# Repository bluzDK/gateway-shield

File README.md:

Bluz Gateway Shield Hardware Files
==========
Bluz is a Development Kit (DK) that implements the Wiring language and talks to the [Particle](https://www.particle.io/) cloud through Bluetooth Low Energy. It can be accessed through a REST API and programmed from a Web IDE.

These files have been made available online through a [Creative Commons Attribution-ShareAlike 3.0](http://creativecommons.org/licenses/by-sa/3.0/) license.

You are welcome to distribute, remix, and use these files for commercial purposes. If you do so, please attribute the original design to Bluz both on the website and on the physical packaging of the product or in the instruction manual. All derivative works must be published under the same or a similar license.

All items are subject to change over time as the product is designed, so make sure you are always looking at the latest information by pulling often.

##Sections
<b>BOM</b>: Current Bill of Materials for the gateway shield.

<b>Datasheets</b>: Datasheets for all major parts on the board.

<b>HW Design</b>: Schematics, board layouts, and other design files.

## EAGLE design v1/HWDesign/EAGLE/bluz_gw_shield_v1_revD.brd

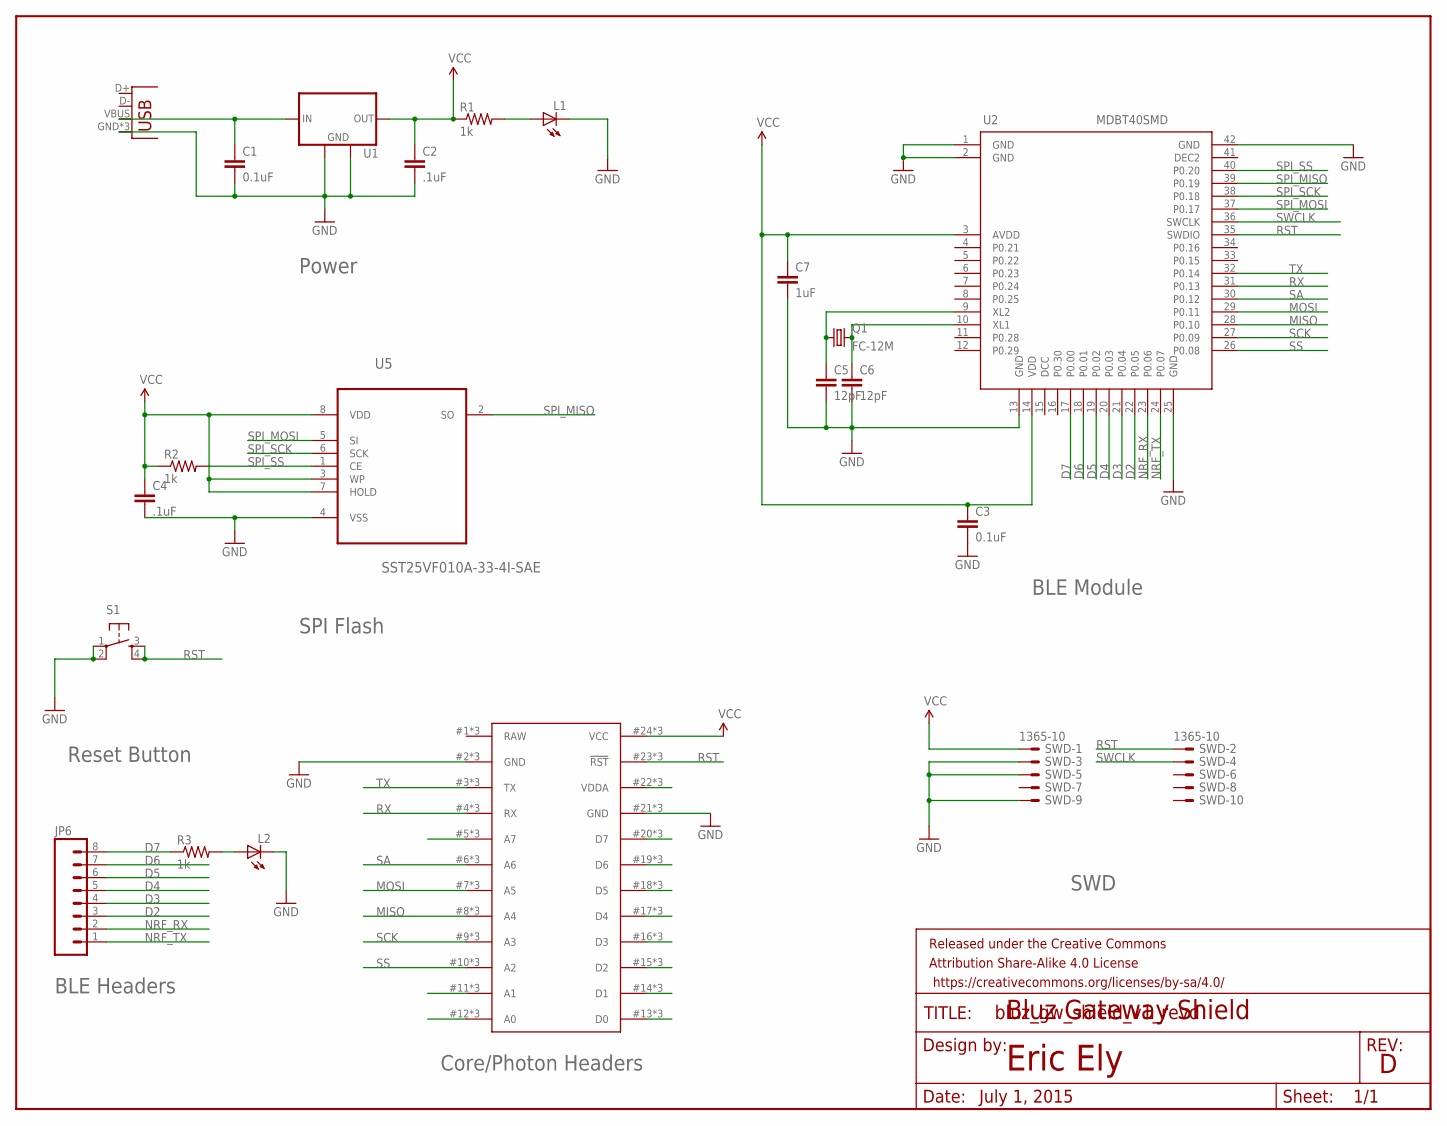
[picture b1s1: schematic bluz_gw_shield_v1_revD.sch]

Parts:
C1, C3: 0.1uF; 0603-CAP
C2, C4: .1uF; 0603-CAP
C5, C6: 12pF; 0603-CAP
C7: 1uF; 0603-CAP
FRAME1: FRAME-LETTER; CREATIVE_COMMONS
J2: USB-MICROB
JP6: M081X08; 1X08
L1, L2: LEDCHIP-LED0603; CHIP-LED0603
Q1: FC-12M
R1, R2, R3: 1k; 0603-RES
S1: TAC_SWITCHSMD; TACTILE_SWITCH_SMD
SWD: 1365-10
U1: MCP1825S-SOT223; SOT223
U2: MDBT40SMD; MDBT40
U4: SPARK_CORE; SPARK_CORE_STACKABLE
U5: SST25VF010A-33-4I-SAE; SOIC127P600X175-8N

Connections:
D2: JP6.3, U2.22 (P0.05)
D3: JP6.4, U2.21 (P0.04)
D4: JP6.5, U2.20 (P0.03)
D5: JP6.6, U2.19 (P0.02)
D6: JP6.7, U2.18 (P0.01)
D7: JP6.8, R3.1, U2.17 (P0.00)
GND: C1.2, C2.2, C3.2, C4.2, C5.2, C6.2, C7.2, J2.GND, J2.MT1 (GND), J2.MT2 (GND), L1.C, L2.C, S1.1, S1.2, SWD.3, SWD.5, SWD.9, U1.2 (GND), U1.4 (GND), U2.1 (GND), U2.2 (GND), U2.13 (GND), U2.25 (GND), U2.42 (GND), U4.2 (GND), U4.21 (GND), U4.#2 (GND), U4.#21 (GND), U4.@2 (GND), U4.@21 (GND), U5.4 (VSS)
MISO: U2.28 (P0.10), U4.8 (A4), U4.#8 (A4), U4.@8 (A4)
MOSI: U2.29 (P0.11), U4.7 (A5), U4.#7 (A5), U4.@7 (A5)
unnamed: C1.1, J2.VBUS, U1.1 (IN)
unnamed: L2.A, R3.2
unnamed: U4.5 (A7), U4.#5 (A7), U4.@5 (A7)
unnamed: U4.11 (A1), U4.#11 (A1), U4.@11 (A1)
unnamed: L1.A, R1.2
unnamed: U4.12 (A0), U4.#12 (A0), U4.@12 (A0)
unnamed: C5.1, Q1.1, U2.9 (XL2)
unnamed: C6.1, Q1.2, U2.10 (XL1)
unnamed: U4.13 (D0), U4.#13 (D0), U4.@13 (D0)
unnamed: U4.14 (D1), U4.#14 (D1), U4.@14 (D1)
unnamed: U4.15 (D2), U4.#15 (D2), U4.@15 (D2)
unnamed: U4.16 (D3), U4.#16 (D3), U4.@16 (D3)
unnamed: U4.17 (D4), U4.#17 (D4), U4.@17 (D4)
unnamed: U4.18 (D5), U4.#18 (D5), U4.@18 (D5)
unnamed: U4.19 (D6), U4.#19 (D6), U4.@19 (D6)
unnamed: U4.20 (D7), U4.#20 (D7), U4.@20 (D7)
unnamed: U4.22 (VDDA), U4.#22 (VDDA), U4.@22 (VDDA)
NRF_RX: JP6.2, U2.23 (P0.06)
NRF_TX: JP6.1, U2.24 (P0.07)
RAW: U4.1 (RAW), U4.#1 (RAW), U4.@1 (RAW)
RST: S1.3, S1.4, SWD.2, U2.35 (SWDIO), U4.23 (!RST), U4.#23 (!RST), U4.@23 (!RST)
RX: U2.31 (P0.13), U4.4 (RX), U4.#4 (RX), U4.@4 (RX)
SA: U2.30 (P0.12), U4.6 (A6), U4.#6 (A6), U4.@6 (A6)
SCK: U2.27 (P0.09), U4.9 (A3), U4.#9 (A3), U4.@9 (A3)
SPI_MISO: U2.39 (P0.19), U5.2 (SO)
SPI_MOSI: U2.37 (P0.17), U5.5 (SI)
SPI_SCK: U2.38 (P0.18), U5.6 (SCK)
SPI_SS: R2.2, U2.40 (P0.20), U5.1 (CE)
SS: U2.26 (P0.08), U4.10 (A2), U4.#10 (A2), U4.@10 (A2)
SWCLK: SWD.4, U2.36 (SWCLK)
TX: U2.32 (P0.14), U4.3 (TX), U4.#3 (TX), U4.@3 (TX)
VCC: C2.1, C3.1, C4.1, C7.1, R1.1, R2.1, SWD.1, U1.3 (OUT), U2.3 (AVDD), U2.14 (VDD), U4.24 (VCC), U4.#24 (VCC), U4.@24 (VCC), U5.3 (WP), U5.7 (HOLD), U5.8 (VDD)

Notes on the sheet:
Core/Photon Headers
Power
BLE Module
SWD
BLE Headers
Eric Ely
Bluz Gateway Shield
July 1, 2015
SPI Flash
Reset Button

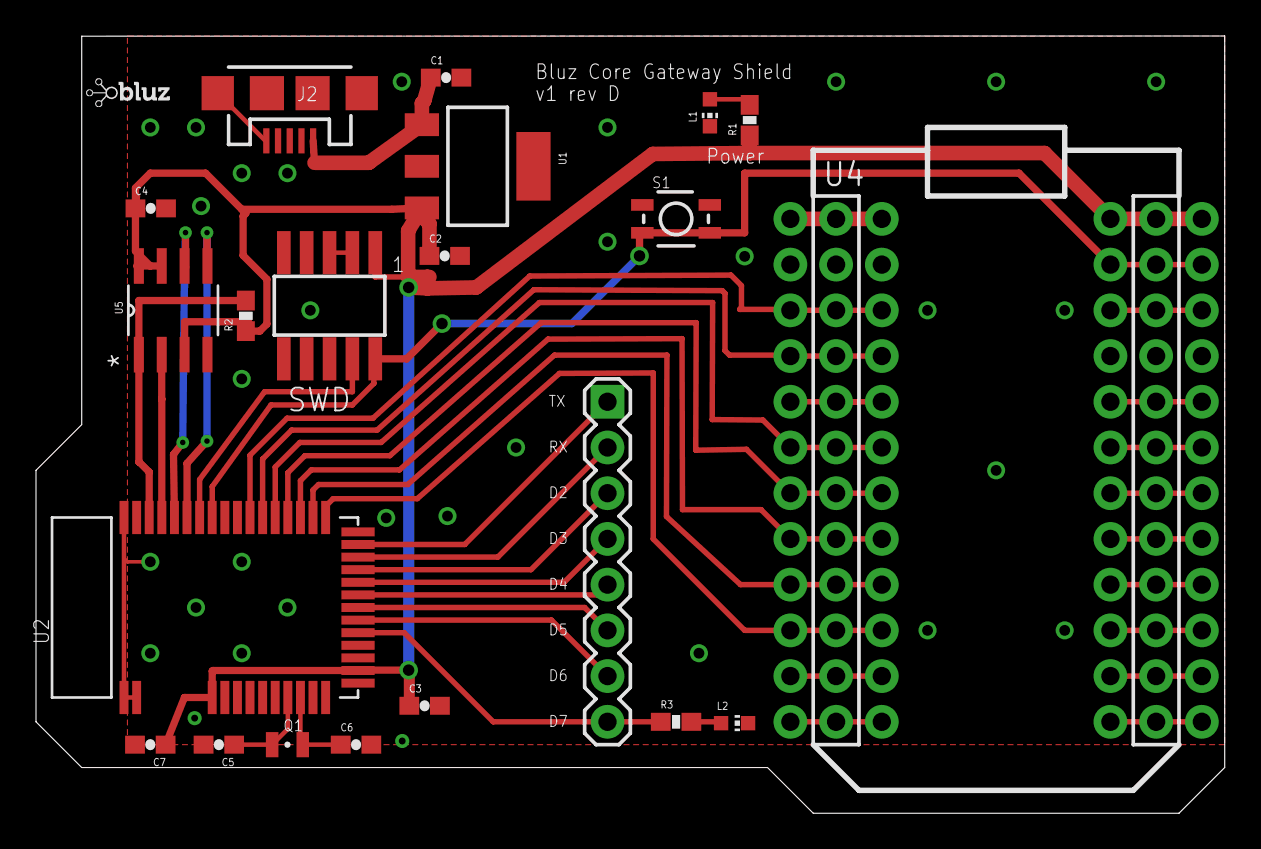
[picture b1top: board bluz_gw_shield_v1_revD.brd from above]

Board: 2 copper layers, 66.0 x 43.2 mm, 23 parts (0 on the bottom side), 41 nets.

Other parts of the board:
U$2: BLUZE_LOGO_LOW_RES

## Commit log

2015-07-01 update BOM
2015-07-03 new schematic. eagle files
2015-08-19 add reset button
2015-09-13 updated BOM, was missing a few things
2016-02-25 newest files from adding the LED on D7 and TX/RX pins

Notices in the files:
parts and their libraries:
SparkFun-Connectors: Licensing: Creative Commons ShareAlike 4.0 International - https://creativecommons.org/licenses/by-sa/4.0
SparkFun-Aesthetics: Released under the Creative Commons Attribution Share-Alike 4.0 License
SparkFun-Aesthetics: https://creativecommons.org/licenses/by-sa/4.0
